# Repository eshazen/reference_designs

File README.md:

# reference_designs
Example projects for educational purposes - no warranty!

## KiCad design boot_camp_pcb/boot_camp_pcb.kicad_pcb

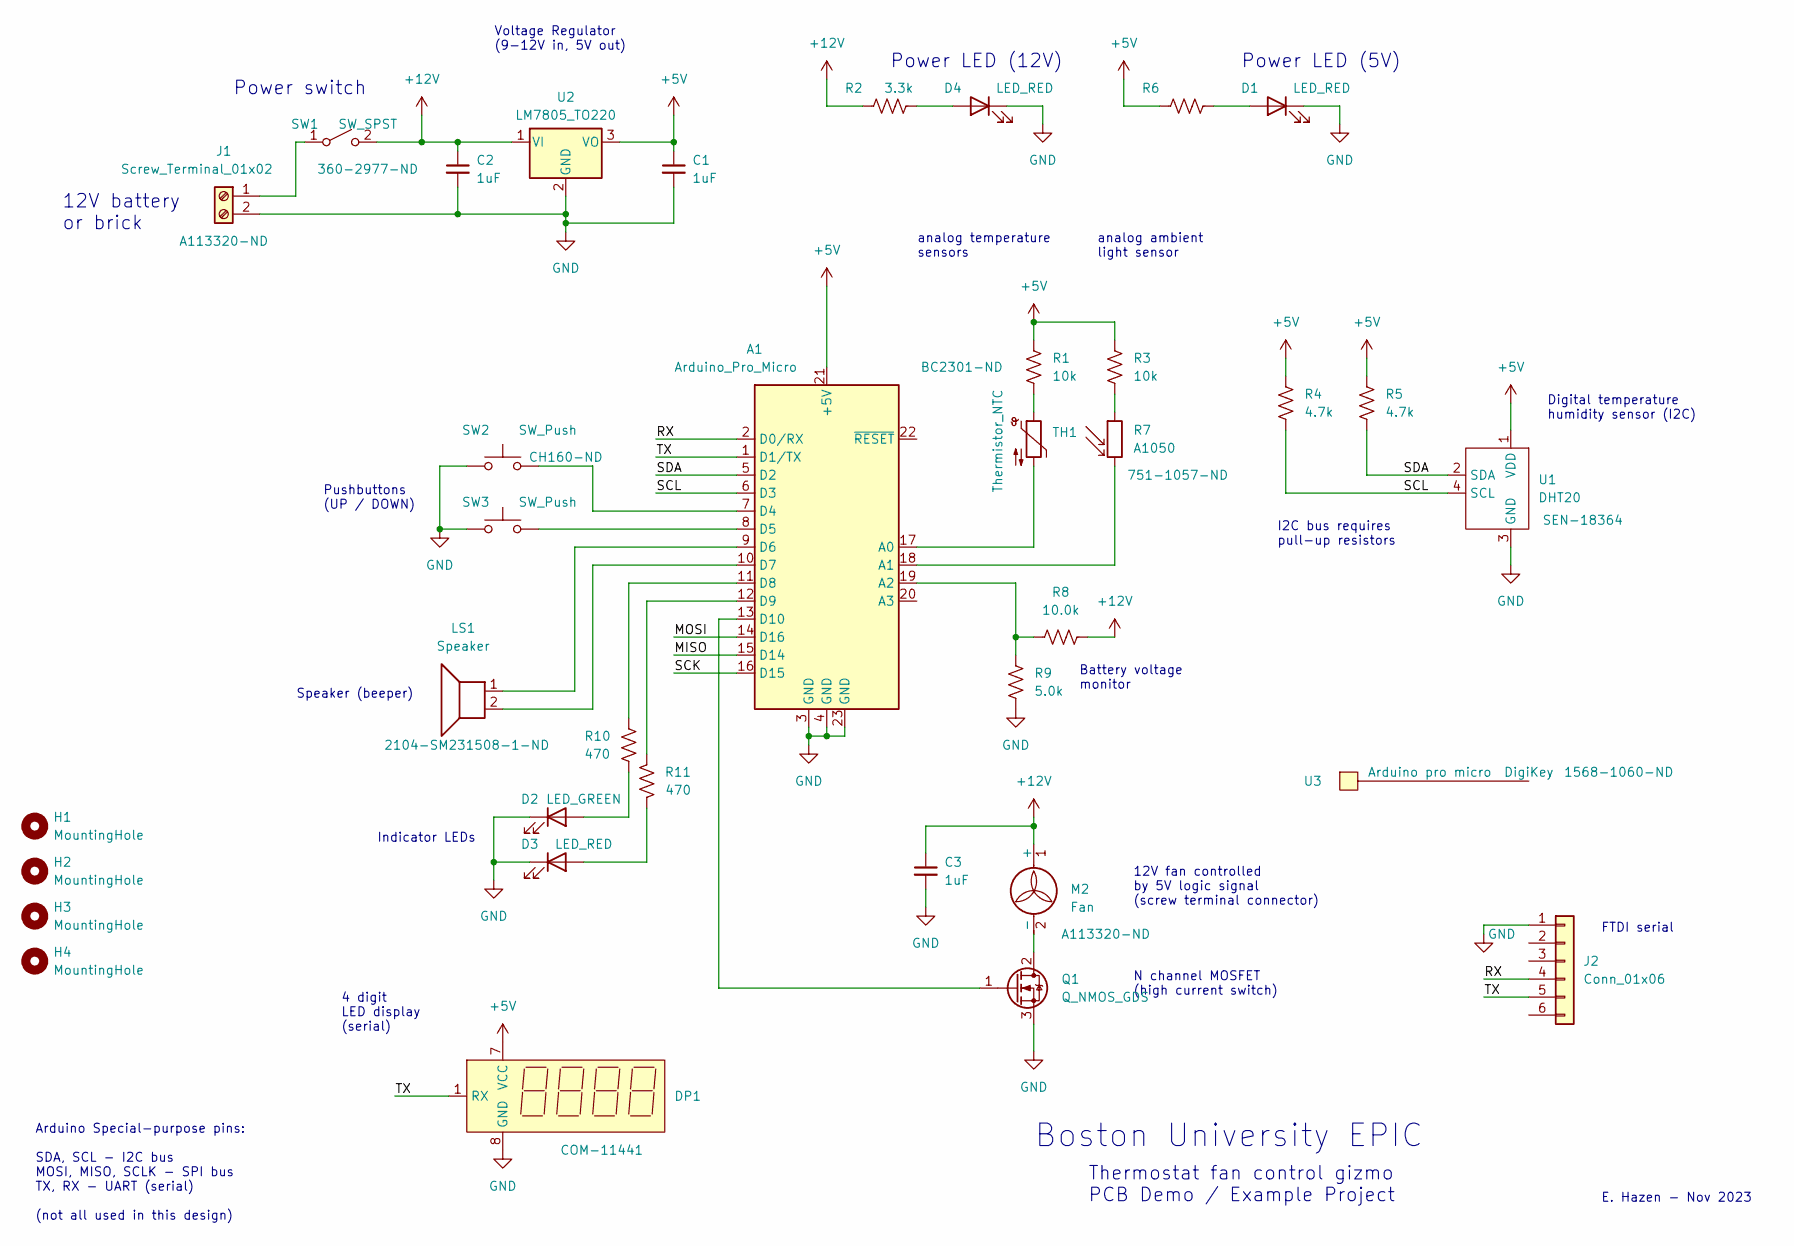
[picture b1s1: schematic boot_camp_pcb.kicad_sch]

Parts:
A1: Arduino_Pro_Micro; pro_micro_socket
C1, C2, C3: 1uF; C_0805_2012Metric
D1, D3, D4: LED_RED; LED_D3.0mm
D2: LED_GREEN; LED_D3.0mm
DP1: sparkfun-serial-led-4digit
H1, H2, H3, H4: MountingHole; MountingHole_3.2mm_M3_Pad
J1: Screw_Terminal_01x02; Wuerth_WR-WTB_64800211622_1x02_P1.50mm_Vertical
J2: Conn_01x06; PinHeader_1x06_P2.54mm_Vertical
LS1: Speaker; SM231508-1_speaker_D22.8P10.0
M2: Fan; Wuerth_WR-WTB_64800211622_1x02_P1.50mm_Vertical
Q1: Q_NMOS_GDS; TO-220-3_Vertical
R1, R3: 10k; R_0805_2012Metric
R2: 3.3k; R_0805_2012Metric
R4, R5: 4.7k; R_0805_2012Metric
R6, R10, R11: 470; R_0805_2012Metric
R7: A1050; LED_D3.0mm
R8: 10.0k; R_0805_2012Metric
R9: 5.0k; R_0805_2012Metric
SW1: SW_SPST; AS11AH_slide_switch
SW2, SW3: SW_Push; SW_Cherry_MX_1.00u_PCB
TH1: Thermistor_NTC; CP_Radial_Tantal_D7.0mm_P2.50mm
U1: DHT20
U2: LM7805_TO220; TO-220-3_Vertical
U3: Arduino pro micro

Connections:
+5V: A1.21 (+5V), C1.1, DP1.7 (VCC), R1.1, R3.1, R4.1, R5.1, R6.1, U1.1 (VDD), U2.3 (VO)
+12V: C2.1, C3.1, M2.1 (+), R2.1, R8.2, SW1.2 (B), U2.1 (VI)
/MISO: A1.15 (D14)
/MOSI: A1.14 (D16)
/RX: A1.2 (D0/RX), J2.4
/SCK: A1.16 (D15)
/SCL: A1.6 (D3), R4.2, U1.4 (SCL)
/SDA: A1.5 (D2), R5.2, U1.2 (SDA)
/TX: A1.1 (D1/TX), DP1.1 (RX), J2.5
GND: A1.3 (GND), A1.4 (GND), A1.23 (GND), C1.2, C2.2, C3.2, D1.1 (K), D2.1 (K), D3.1 (K), D4.1 (K), DP1.8 (GND), J1.2, J2.1, Q1.3 (S), R9.1, SW2.1, SW3.1, U1.3 (GND), U2.2 (GND)
unnamed: A1.17 (A0), TH1.2
unnamed: A1.18 (A1), R7.2
unnamed: A1.19 (A2), R8.1, R9.2
unnamed: A1.7 (D4), SW2.2
unnamed: A1.8 (D5), SW3.2
unnamed: A1.9 (D6), LS1.1
unnamed: A1.10 (D7), LS1.2
unnamed: A1.11 (D8), R10.2
unnamed: A1.12 (D9), R11.2
unnamed: A1.13 (D10), Q1.1 (G)
unnamed: D1.2 (A), R6.2
unnamed: D2.2 (A), R10.1
unnamed: D3.2 (A), R11.1
unnamed: D4.2 (A), R2.2
unnamed: J1.1, SW1.1 (A)
unnamed: M2.2 (-), Q1.2 (D)
unnamed: R1.2, TH1.1
unnamed: R3.2, R7.1

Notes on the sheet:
analog ambient light sensor
12V fan controlled by 5V logic signal (screw terminal connector)
Thermostat fan control gizmo PCB Demo / Example Project
E. Hazen - Nov 2023
Power LED (5V)
12V battery or brick
Arduino Special-purpose pins: SDA, SCL - I2C bus MOSI, MISO, SCLK - SPI bus TX, RX - UART (serial) (not all used in this design)
I2C bus requires pull-up resistors
Speaker (beeper)
Battery voltage monitor
Digital temperature humidity sensor (I2C)
4 digit LED display (serial)
FTDI serial
Boston University EPIC
Power switch
Power LED (12V)
Indicator LEDs
Voltage Regulator (9-12V in, 5V out)
Pushbuttons (UP / DOWN)
N channel MOSFET (high current switch)
analog temperature sensors

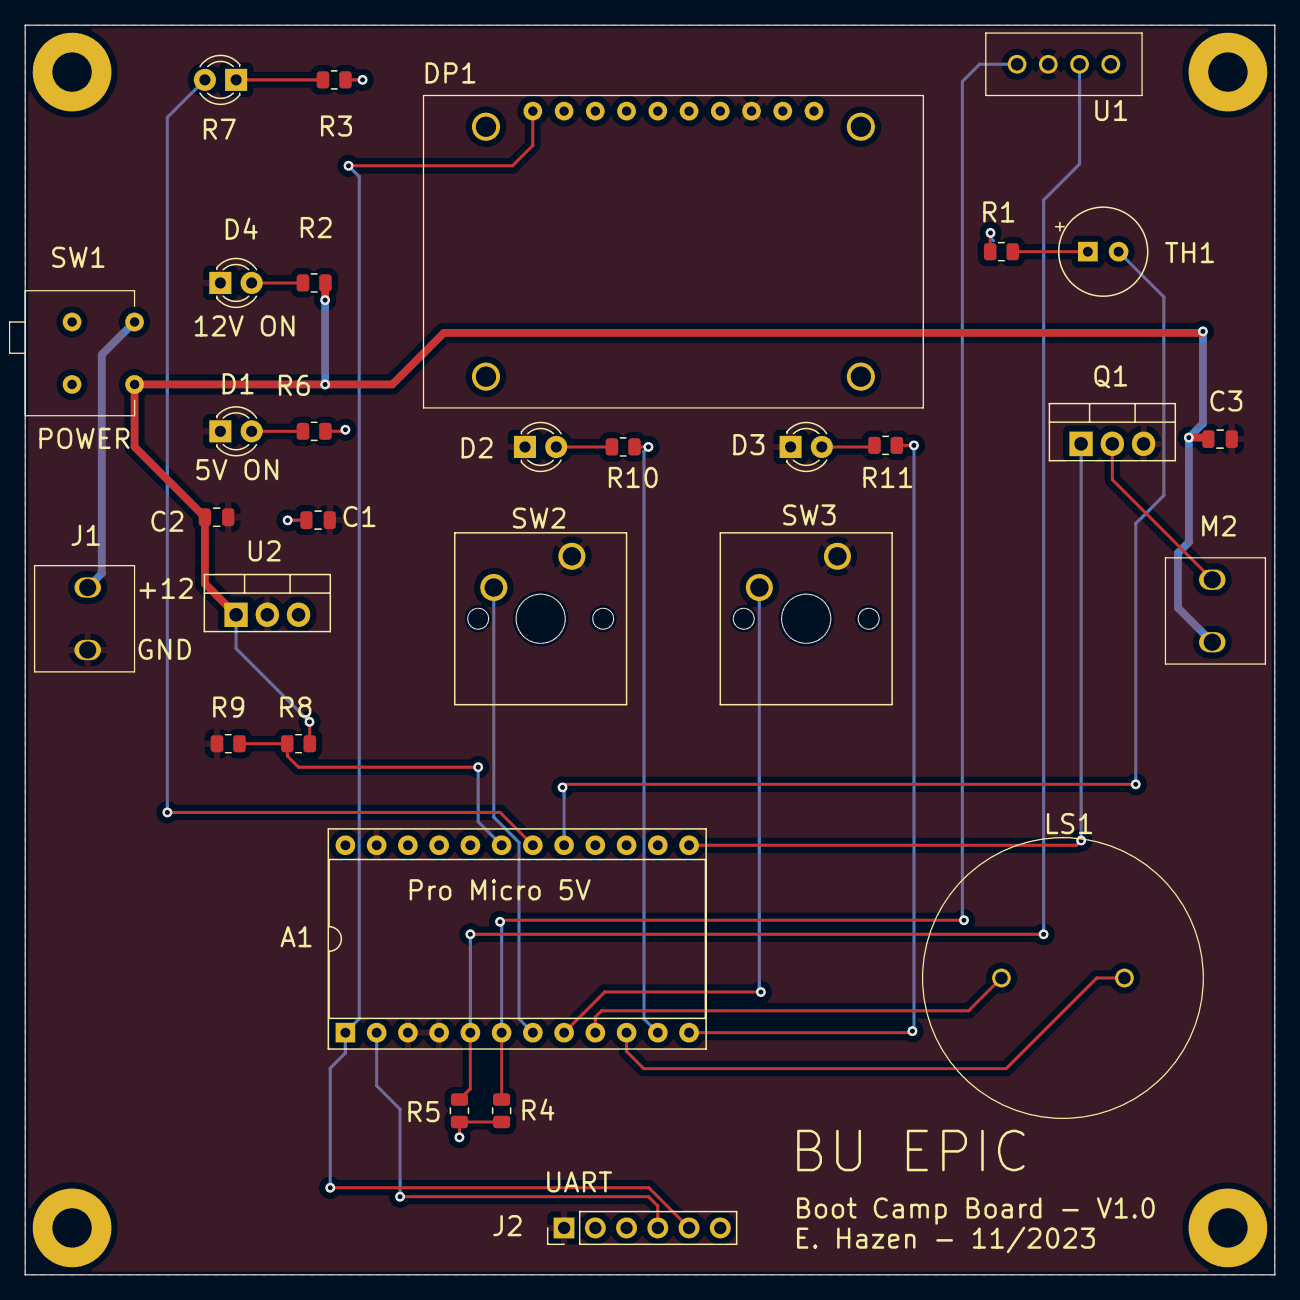
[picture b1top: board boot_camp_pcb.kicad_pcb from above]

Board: 2 copper layers, 101.6 x 101.6 mm, 35 parts (0 on the bottom side), 25 nets.

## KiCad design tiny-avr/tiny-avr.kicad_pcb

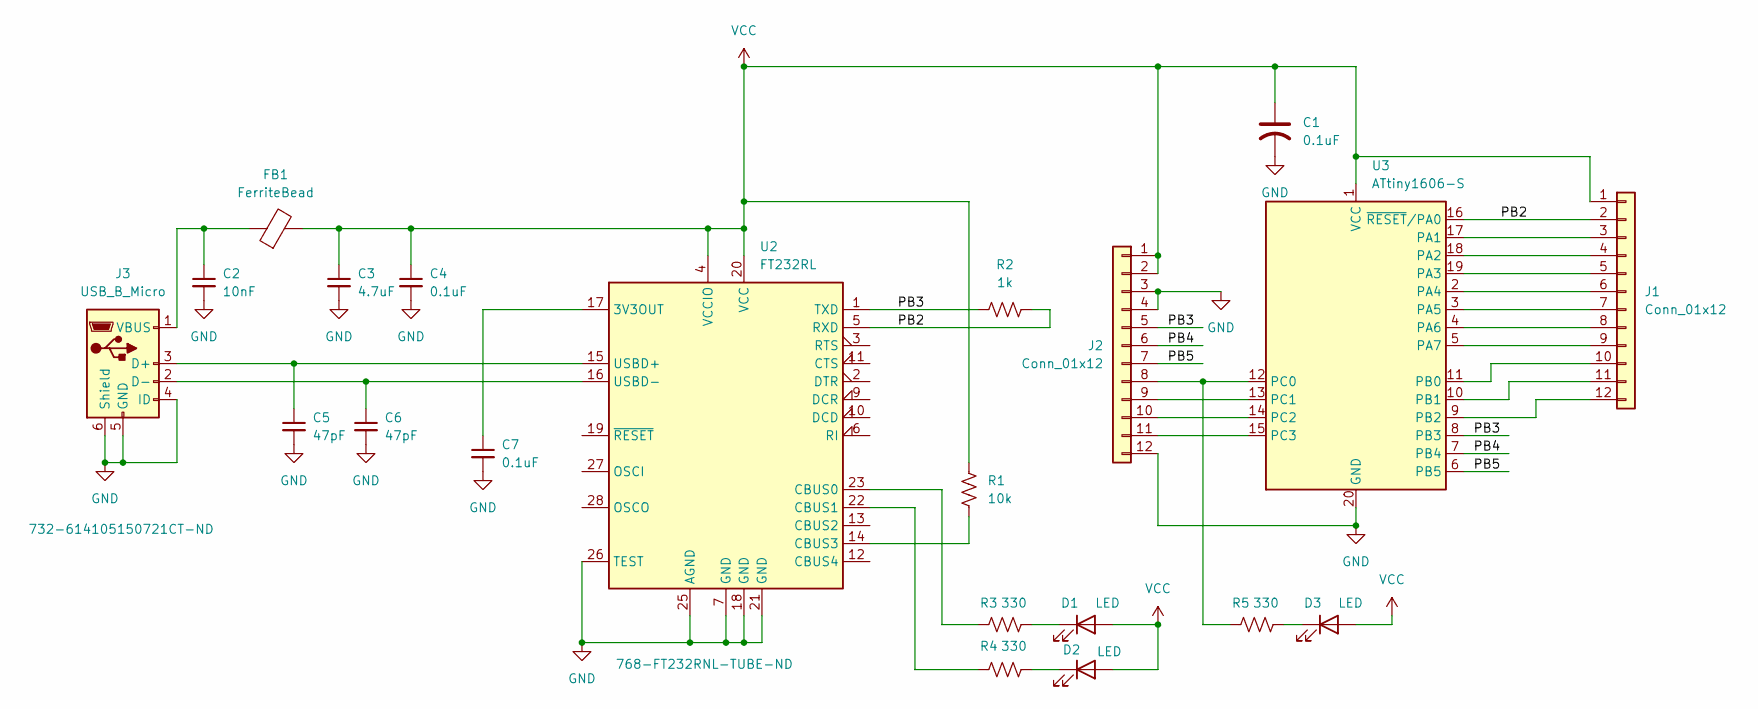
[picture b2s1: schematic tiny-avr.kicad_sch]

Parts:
C1, C4, C7: 0.1uF; C_0603_1608Metric_Pad1.08x0.95mm_HandSolder
C2: 10nF; C_0603_1608Metric_Pad1.08x0.95mm_HandSolder
C3: 4.7uF; C_0603_1608Metric_Pad1.08x0.95mm_HandSolder
C5, C6: 47pF; C_0603_1608Metric_Pad1.08x0.95mm_HandSolder
D1, D2, D3: LED; LED_0603_1608Metric_Pad1.05x0.95mm_HandSolder
FB1: FerriteBead; L_0603_1608Metric_Pad1.05x0.95mm_HandSolder
J1, J2: Conn_01x12; PinHeader_1x12_P2.54mm_Vertical
J3: USB_B_Micro; USB_Micro-B_Wuerth_614105150721_Vertical_CircularHoles
R1: 10k; R_0603_1608Metric_Pad0.98x0.95mm_HandSolder
R2: 1k; R_0603_1608Metric_Pad0.98x0.95mm_HandSolder
R3, R4, R5: 330; R_0603_1608Metric_Pad0.98x0.95mm_HandSolder
U2: FT232RL; SSOP-28_5.3x10.2mm_P0.65mm
U3: ATtiny1606-S; SOIC-20W_7.5x12.8mm_P1.27mm

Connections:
/PB2: J1.2, R2.2, U2.5 (RXD), U3.16 (~RESET/PA0)
/PB3: J2.5, R2.1, U2.1 (TXD), U3.8 (PB3)
/PB4: J2.6, U3.7 (PB4)
/PB5: J2.7, U3.6 (PB5)
GND: C1.2, C2.2, C3.2, C4.2, C5.2, C6.2, C7.2, J2.3, J2.4, J2.12, J3.4 (ID), J3.5 (GND), J3.6 (Shield), U2.7 (GND), U2.18 (GND), U2.21 (GND), U2.25 (AGND), U2.26 (TEST), U3.20 (GND)
unnamed: D1.1 (K), R3.2
unnamed: D2.1 (K), R4.2
unnamed: D3.1 (K), R5.2
unnamed: J1.3, U3.17 (PA1)
unnamed: J1.4, U3.18 (PA2)
unnamed: J1.5, U3.19 (PA3)
unnamed: J1.6, U3.2 (PA4)
unnamed: J1.7, U3.3 (PA5)
unnamed: J1.8, U3.4 (PA6)
unnamed: J1.9, U3.5 (PA7)
unnamed: J1.10, U3.11 (PB0)
unnamed: J1.11, U3.10 (PB1)
unnamed: J1.12, U3.9 (PB2)
unnamed: J2.8, R5.1, U3.12 (PC0)
unnamed: J2.9, U3.13 (PC1)
unnamed: J2.10, U3.14 (PC2)
unnamed: J2.11, U3.15 (PC3)
unnamed: C5.1, J3.3 (D+), U2.15 (USBD+)
unnamed: C6.1, J3.2 (D-), U2.16 (USBD-)
unnamed: C2.1, FB1.1, J3.1 (VBUS)
unnamed: C7.1, U2.17 (3V3OUT)
unnamed: R3.1, U2.23 (CBUS0)
unnamed: R4.1, U2.22 (CBUS1)
unnamed: R1.2, U2.14 (CBUS3)
VCC: C1.1, C3.1, C4.1, D1.2 (A), D2.2 (A), D3.2 (A), FB1.2, J1.1, J2.1, J2.2, R1.1, U2.4 (VCCIO), U2.20 (VCC), U3.1 (VCC)

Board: 2 copper layers, 21 parts (10 on the bottom side), 30 nets, no tracks yet.

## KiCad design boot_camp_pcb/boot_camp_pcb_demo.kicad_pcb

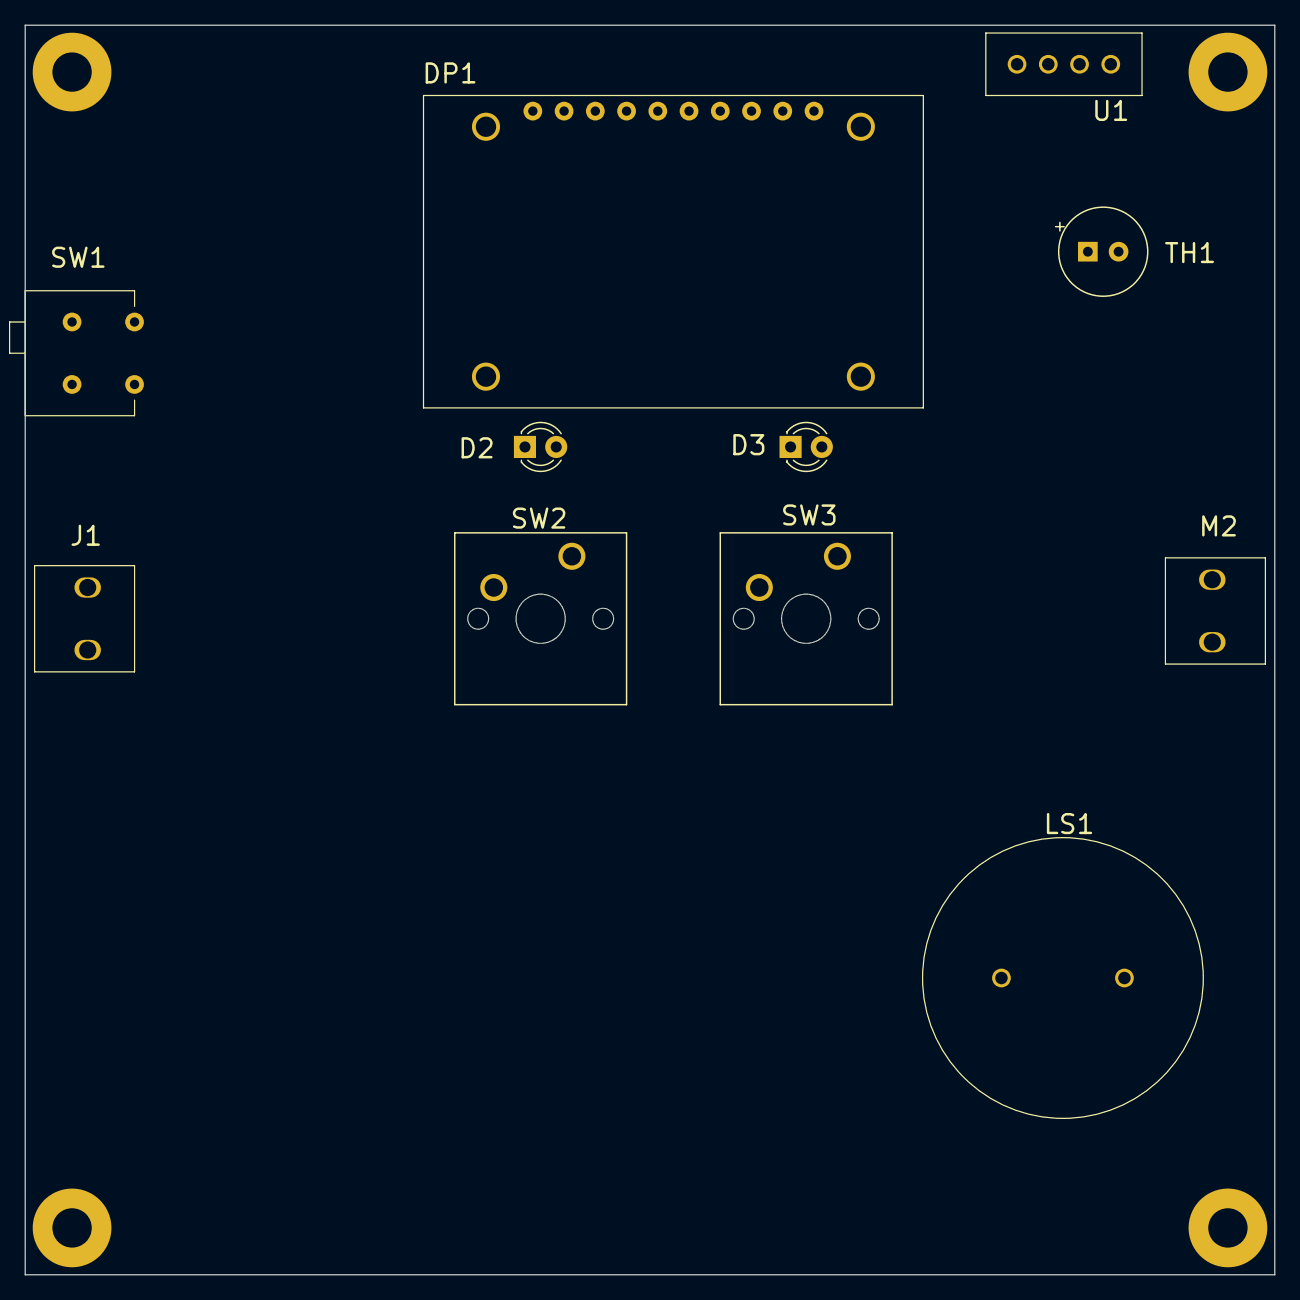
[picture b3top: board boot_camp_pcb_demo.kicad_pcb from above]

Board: 2 copper layers, 101.6 x 101.6 mm, 15 parts (0 on the bottom side), 4 nets, no tracks yet.

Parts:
D2: LED_GREEN; LED_D3.0mm
D3: LED_RED; LED_D3.0mm
DP1: sparkfun-serial-led-4digit
H1, H2, H3, H4: MountingHole; MountingHole_3.2mm_M3_Pad
J1: Screw_Terminal_01x02; Wuerth_WR-WTB_64800211622_1x02_P1.50mm_Vertical
LS1: Speaker; SM231508-1_speaker_D22.8P10.0
M2: Fan; Wuerth_WR-WTB_64800211622_1x02_P1.50mm_Vertical
SW1: SW_SPST; AS11AH_slide_switch
SW2, SW3: SW_Push; SW_Cherry_MX_1.00u_PCB
TH1: Thermistor_NTC; CP_Radial_Tantal_D7.0mm_P2.50mm
U1: DHT20

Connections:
+5V: DP1.7 (VCC), U1.1 (VDD)
+12V: M2.1 (+), SW1.2 (B)
GND: D2.1 (K), D3.1 (K), DP1.8 (GND), J1.2, SW2.1, SW3.1, U1.3 (GND)
unnamed: J1.1, SW1.1 (A)

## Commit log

2023-11-09 Initial commit from talks/designs
2023-11-09 tweak
2023-11-09 finish pcb, make demo
2023-11-12 temporary fix 3D models in PCB
2025-06-25 start tiny avr breakout
2025-06-26 working on tiny
2025-09-16 Update to KiCAD 9
